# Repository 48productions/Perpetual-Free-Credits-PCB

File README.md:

# Perpetual Free Credits PCB (a.k.a. the PFC PCB)
**A Non-Destructive Arcade Game Coinup Mod PCB**

It keeps compatible games fully credited up at all times, perfect for arcade games that either lack a Free Play mode, or are missing features in Free Play mode that are present in Credit mode.

It's designed solely for games with a **credit limit** that control a **coin blocker** relay based on this limit. If the game isn't at its credit limit, it powers the coin blocker relay (and thus the PFC PCB), which inserts credits until the credit limit is reached, and the game turns off the coin blocker relay. 

---
## Compatibility/Installation

### Compatibility List
This board is **compatible** with:
 - ✅ CHUNITHM (tested on NEW!! and many pre-NEW!! versions)
 - ✅ Middle Earth (Atari pinball)
 - ✅ crossbeats REV. (tested on SUNRISE S2)*
 - ✅ Probably a lot of others :D

This board is **incompatible** with games that have a coin blocker relay, but no credit limit:
 - ❌ SOUND VOLTEX (tested on EXCEED GEAR)
 - ❌ jubeat (tested on festo)

An alternative design is being considered for these games.

*\* crossbeats: This board will continuously insert credits in test mode, since the game always powers the coin blocker in test mode regardless of the credit limit.*

### Checking Compatibility
**For games not on the list, your game MUST:**

 - **Have a coin blocker relay** on the coin acceptor (mostly found in older or JP-import games)
 
 - Power said relay with *10-30VDC* or *5VDC*
 
 - Turn on the relay when the game enters attract mode (you'll hear it click on)
 
 - **Have a credit limit, and will turn off the Coin Blocker when this limit is reached** (this is not always the case)!

In modern games, the relay can usually be toggled on/off in the game's test mode (look for an "Output Test" menu).

---
## Alternative Designs
[ChunUp](https://github.com/progmem/ChunUp) is a very clean and cost-reduced design geared specifically for CHUNITHM cabinets.

---
## Fabrication
**[See FABRICATION.md](FABRICATION.md) for instructions on how to fabricate this design!**

---
## Installation
**[See INSTALLATION.md](INSTALLATION.md) for instructions on how to install this board in your game!**

---
## Troubleshooting
**[See TROUBLESHOOTING.md](TROUBLESHOOTING.md) for instructions on how to troubleshoot common issues!**

---
## No Really How Does This Work

This board connects to the power wires for the Coin Blocker relay on your arcade cabinet, if it has one, through voltage regulator U2. Normally, this relay is attached to the game's coin acceptor and will reject any coins (even valid ones) whenever the game is not ready to accept coins (game powered off, maximum credit limit reached, etc).

When the game is ready to accept coins, it powers the coin blocker to let coins in. This turns on the PFC board, which will repeatedly trigger the game's coin switch using timer U1 through opto isolator U3. When the game hits the maximum credit limit, it powers off the coin relay (and thus the PFC board), which stops inserting coins. This way, your game is always credited up and ready to play.

Timing of the pulses is controlled by capacitor C1, resistor R2 (20k, time between pulses), and resistor/potentiometer R1/VR1 (1k + 0-10k, pulse frequency).

---
## Credits/Disclaimers

This project came about because of a few relevant conversations in the awesome western arcade rhythm game community, and the general concept/design was discussed by several community members.

You are installing this board at your own risk, and I cannot be held liable for damages, destruction, magic smoke escaping, or otherwise.

For arcade games on an official online network, your network may not allow the use of this board or similar mods. As such, usage of this board in these circumstances isn't recommended.

*Any games mentioned are properties of their respective owners. This design was produced independently of them, and is in no way endorsed or officially supported.*

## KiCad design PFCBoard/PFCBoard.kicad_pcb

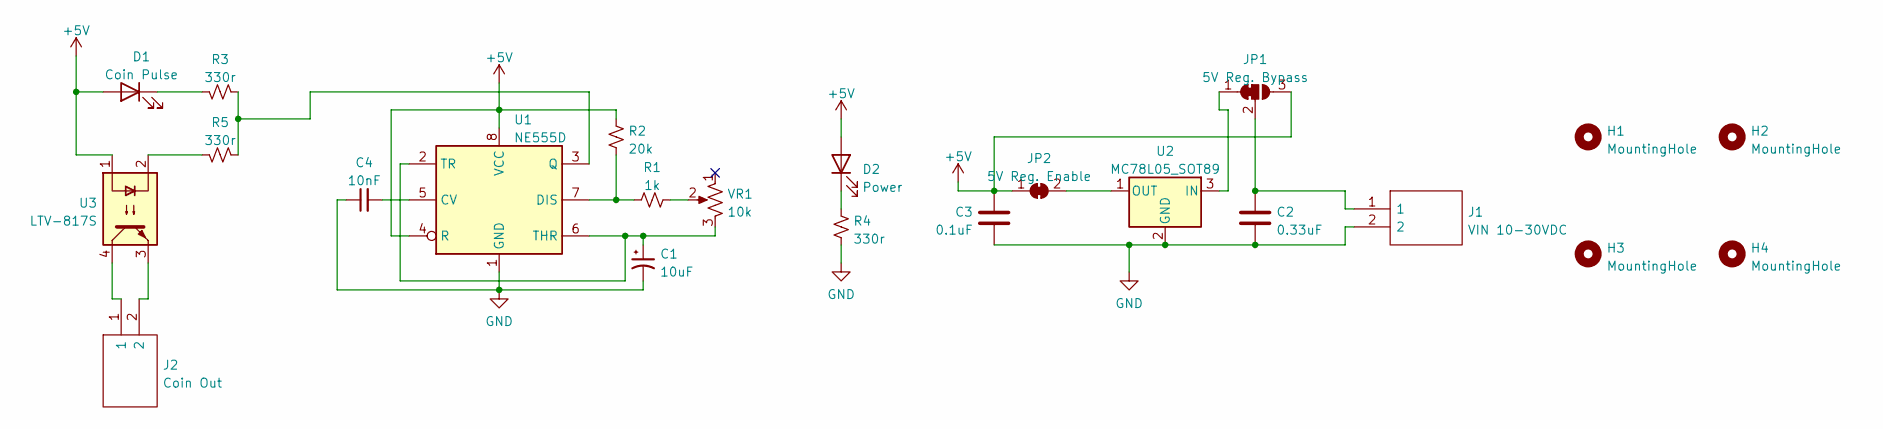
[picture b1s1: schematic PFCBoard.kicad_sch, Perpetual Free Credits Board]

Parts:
C1: 10uF; CP_Elec_4x4.5
C2: 0.33uF; C_1206_3216Metric_Pad1.33x1.80mm_HandSolder
C3: 0.1uF; C_1206_3216Metric_Pad1.33x1.80mm_HandSolder
C4: 10nF; C_1206_3216Metric_Pad1.33x1.80mm_HandSolder
D1: Coin Pulse; LED_1206_3216Metric_Pad1.42x1.75mm_HandSolder
D2: Power; LED_1206_3216Metric_Pad1.42x1.75mm_HandSolder
H1, H2, H3, H4: MountingHole; MountingHole_3mm
J1: VIN 10-30VDC; 1713017; Manufacturer_Part_Number 1713017; Mouser Part Number 651-1713017
J2: Coin Out; 1713017; Manufacturer_Part_Number 1713017; Mouser Part Number 651-1713017
JP1: 5V Reg. Bypass; SolderJumper-3_P1.3mm_Bridged12_Pad1.0x1.5mm
JP2: 5V Reg. Enable; SolderJumper-2_P1.3mm_Bridged_Pad1.0x1.5mm
R1: 1k; R_1206_3216Metric_Pad1.30x1.75mm_HandSolder
R2: 20k; R_1206_3216Metric_Pad1.30x1.75mm_HandSolder
R3, R4, R5: 330r; R_1206_3216Metric_Pad1.30x1.75mm_HandSolder
U1: NE555D; SOIC-8_3.9x4.9mm_P1.27mm
U2: MC78L05_SOT89; SOT-89-3
U3: LTV-817S; SMDIP-4_W9.53mm
VR1: 10k; Potentiometer_Bourns_TC33X_Vertical

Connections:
+5V: C3.1, D1.2 (A), D2.2 (A), JP1.3 (B), JP2.1 (A), R2.1, U1.4 (R), U1.8 (VCC), U3.1
GND: C1.2, C2.2, C3.2, C4.1, J1.2, R4.2, U1.1 (GND), U2.2 (GND)
unnamed: C1.1, U1.2 (TR), U1.6 (THR), VR1.3
unnamed: C2.1, J1.1, JP1.2 (C)
unnamed: C4.2, U1.5 (CV)
unnamed: D1.1 (K), R3.2
unnamed: D2.1 (K), R4.1
unnamed: J2.1, U3.4
unnamed: J2.2, U3.3
unnamed: JP1.1 (A), U2.3 (IN)
unnamed: JP2.2 (B), U2.1 (OUT)
unnamed: R1.1, R2.2, U1.7 (DIS)
unnamed: R1.2, VR1.2
unnamed: R3.1, R5.1, U1.3 (Q)
unnamed: R5.2, U3.2

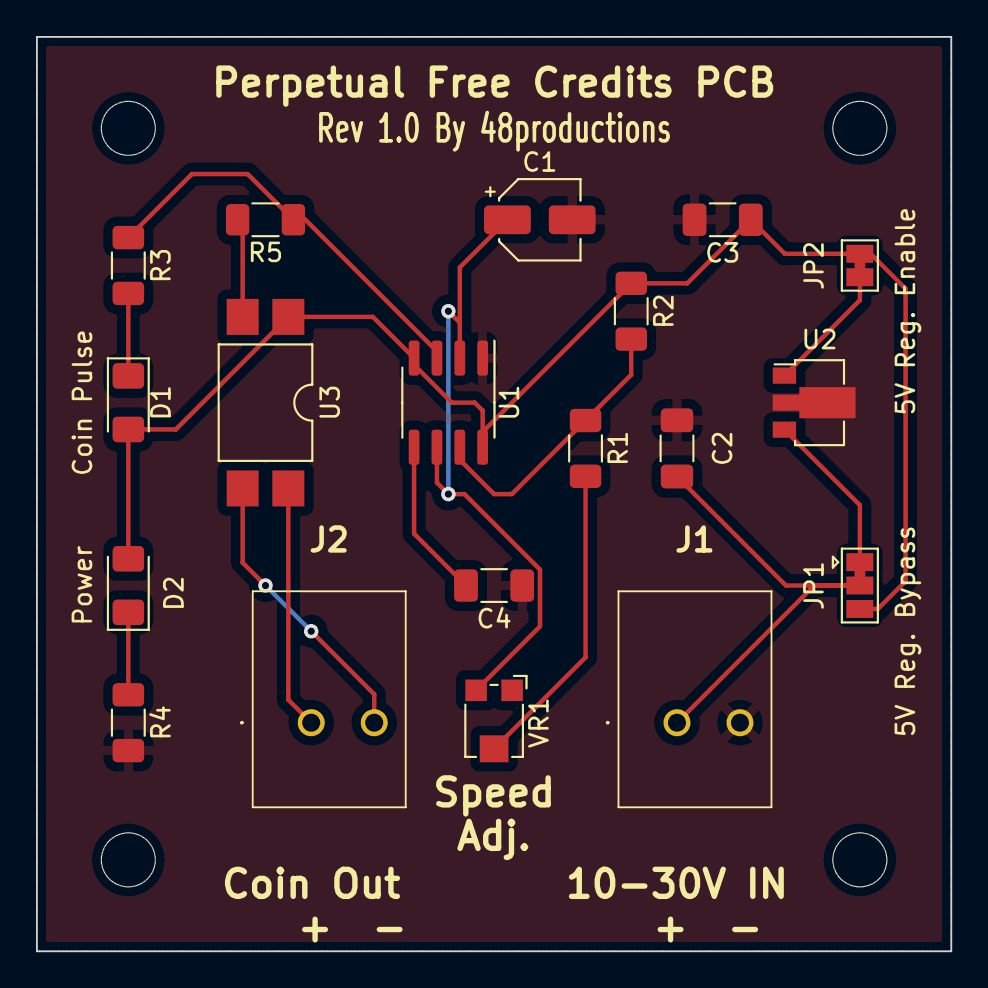
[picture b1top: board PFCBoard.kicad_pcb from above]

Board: 2 copper layers, 50.8 x 50.8 mm, 23 parts (0 on the bottom side), 15 nets.

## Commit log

2022-12-26 Schematic Rev v0.1
2022-12-31 Add voltage selection, pre-rendered schematic
2023-01-12 PCB design, schematic/readme tweaks
2023-02-11 PFCBoard v1 Gerbers
2023-03-11 More/Better Documentation
